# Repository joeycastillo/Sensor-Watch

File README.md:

The Sensor Watch
================

The [Sensor Watch](https://www.sensorwatch.net) is a board replacement for the classic Casio F-91W wristwatch. It is powered by a Microchip SAM L22 microcontroller with built-in segment LCD controller. You can write your own programs for the watch using the provided watch library, program the watch over USB using the built-in UF2 bootloader, and then install the board in your existing watch case to run your own software on your wrist.

Features:
* ARM Cortex M0+ microcontroller
* 32KHz crystal for real-time clock with alarm function
* Ten digit segment LCD, plus five indicator segments
* Three interrupt capable buttons
* Red / green PWM’able LED backlight
* Optional piezo buzzer (requires some light soldering)
* On-board USB Micro B connector
* Reset button with double-tap UF2 bootloader
* Nine-pin flex PCB connector

You may have noticed that there are no sensors on this board. That is by design: rather than pick sensors for you, the goal is to add a tiny flexible PCB with the sensors YOU want, and interface them over the nine-pin connector. The connector provides the following options for power and connectivity:

* 3V power (nominal voltage from a CR2016 coin cell, can drop to ~2.7V)
* An I²C interface with built-in pull-up resistors
* Five general purpose IO pins, which can be configured as:
    * Five analog inputs
    * Five interrupt-capable digital inputs, with internal pull-up or pull-down resistors
    * Five digital outputs
    * SPI controller (with one spare analog / GPIO pin leftover)
    * One UART TX/RX pair (with three GPIO leftover)
    * Up to four PWM pins on two independent TC instances
    * Two external wake inputs that can wake from the ultra-low-power BACKUP mode

| **Pin** | **Digital** | **Interrupt**   | **Analog**    | **I2C**             | **SPI**              | **UART**                 | **PWM**  | **Ext. Wake** |
| :-----: | :---------: | :-------------: | :-----------: | :-----------------: | :------------------: | :----------------------: | :------: | :-----------: |
| **A0**  | PB04        | EIC/EXTINT\[4\] | ADC/AIN\[12\] | —                   | —                    | —                        | —        | —             |
| **SCL** | —           | —               | —             | SCL<br>SERCOM1\[1\] | —                    | —                        | —        | —             |
| **SDA** | —           | —               | —             | SDA<br>SERCOM1\[0\] | —                    | —                        | —        | —             |
| **A1**  | PB01        | EIC/EXTINT\[1\] | ADC/AIN\[9\]  | —                   | SCK<br>SERCOM3\[3\]  | RX<br>SERCOM3\[3\]       | TC3\[1\] | —             |
| **A2**  | PB02        | EIC/EXTINT\[2\] | ADC/AIN\[10\] | —                   | MOSI<br>SERCOM3\[0\] | TX or RX<br>SERCOM3\[0\] | TC2\[0\] | RTC/IN\[1\]   |
| **A3**  | PB03        | EIC/EXTINT\[3\] | ADC/AIN\[11\] | —                   | CS<br>SERCOM3\[1\]   | RX<br>SERCOM3\[1\]       | TC2\[1\] | —             |
| **A4**  | PB00        | EIC/EXTINT\[0\] | ADC/AIN\[8\]  | —                   | MISO<br>SERCOM3\[2\] | TX or RX<br>SERCOM3\[2\] | TC3\[0\] | RTC/IN\[0\]   |

These tiny “sensor boards” have a set outline, and the available area for your electronics is quite small (5.7 × 5.7 × 1 mm). Still, this is plenty of room for an environmental sensor, MEMS accelerometer or magnetometer and a couple of decoupling capacitors. Note that you will likely be limited to QFN and LGA type parts; SOICs are too large, and even SSOP packages are generally too thick. You can find reference designs for several sensor boards in the `PCB/Sensor Boards` directory within this repository.

Getting code on the watch
-------------------------
The watch library in this repository is very work-in-progress, but it should allow you to get started. To create a new project, copy the “starter-project” folder in the apps folder, and write your code in the app.c file.

You will need to install [the GNU Arm Embedded Toolchain](https://developer.arm.com/tools-and-software/open-source-software/developer-tools/gnu-toolchain/gnu-rm/downloads/) to build projects for the watch. The watch library has been tested with the `9-2019-q4-major` version and the `10.3-2021.07` versions. If you're using Debian or Ubuntu, it should be sufficient to `apt install gcc-arm-none-eabi`.

To build your project, open your terminal and navigate to the project's `make` folder, then type `make`.

To install the project onto your Sensor Watch board, plug the watch into your USB port and double tap the tiny Reset button on the back of the board. You should see the LED light up red and begin pulsing. (If it does not, make sure you didn’t plug the board in upside down). Once you see the “WATCHBOOT” drive appear on your desktop, type `make install`. This will convert your compiled program to a UF2 file, and copy it over to the watch.

Using the Movement framework
----------------------------
If you just want to make minor modifications and use existing code, start with the `movement` directory. You can build the default watch firmware with:

```
cd movement/make
make
```

Then copy `movement/make/build/watch.uf2` to your watch. If you'd like to modify which faces are built, see `movement_config.h`.

You may want to test out changes in the emulator first. To do this, you'll need to install [emscripten](https://emscripten.org/), then run:

```
cd movement/make
emmake make
python3 -m http.server -d build-sim
```

Finally, visit [watch.html](http://localhost:8000/watch.html) to see your work.

Hardware Schematics and PCBs
----------------------------

| Name | Color | Schematic | Gerbers |
| ---- | ----- | --------- | ------- |
| Sensorwatch Lite | RED   | [PCB/Main Boards/OSO-SWAT-B1](PCB/Main%20Boards/OSO-SWAT-B1) | [OSO-SWAT-B1-03](PCB/Main%20Boards/OSO-SWAT-B1/OSO-SWAT-B1-03.zip) |
| Sensorwatch      | GREEN | [OSO-SWAT-A1-05](PCB/Main%20Boards/OSO-SWAT-A1/OSO-SWAT-A1-05.sch) (Eagle format) | ? |
| Sensorwatch Pro  | TBD   | TBD  | TBD |

License
-------
Different components of the project are licensed differently, see [LICENSE.md](https://github.com/joeycastillo/Sensor-Watch/blob/main/LICENSE.md).

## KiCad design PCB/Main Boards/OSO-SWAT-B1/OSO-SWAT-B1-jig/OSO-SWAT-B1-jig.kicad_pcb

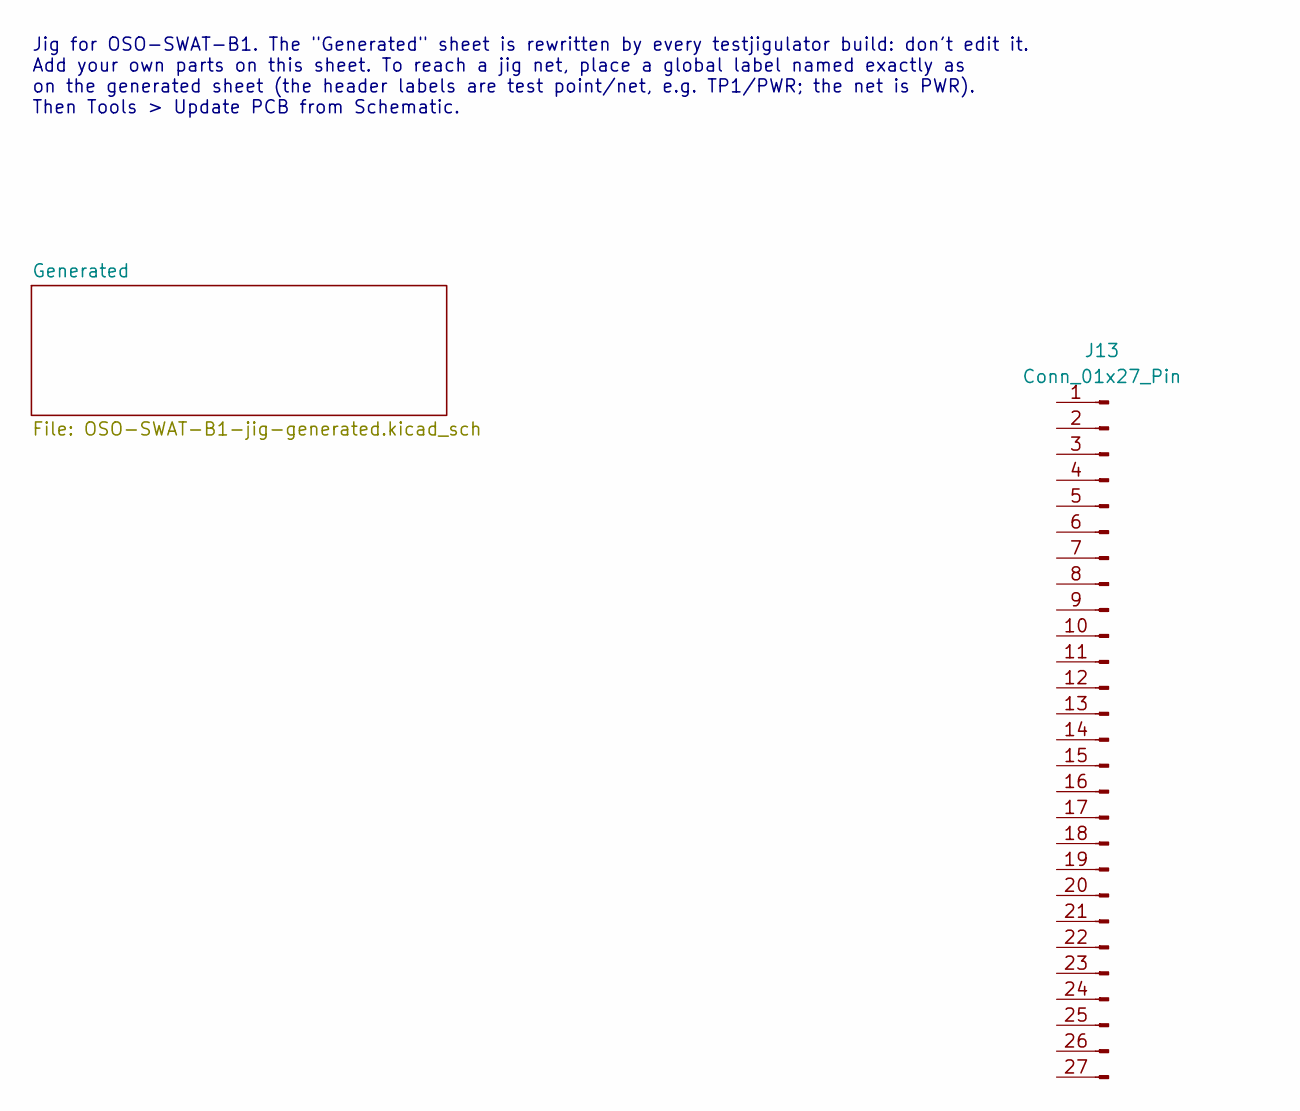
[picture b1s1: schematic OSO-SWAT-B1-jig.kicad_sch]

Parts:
J13: Conn_01x27_Pin; testjig-zebra-footprint

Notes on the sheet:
Jig for OSO-SWAT-B1. The "Generated" sheet is rewritten by every testjigulator build: don't edit it. Add your own parts on this sheet. To reach a jig net, place a global label named exactly as on the generated sheet (the header labels are test point/net, e.g. TP1/PWR; the net is PWR). Then Tools > 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

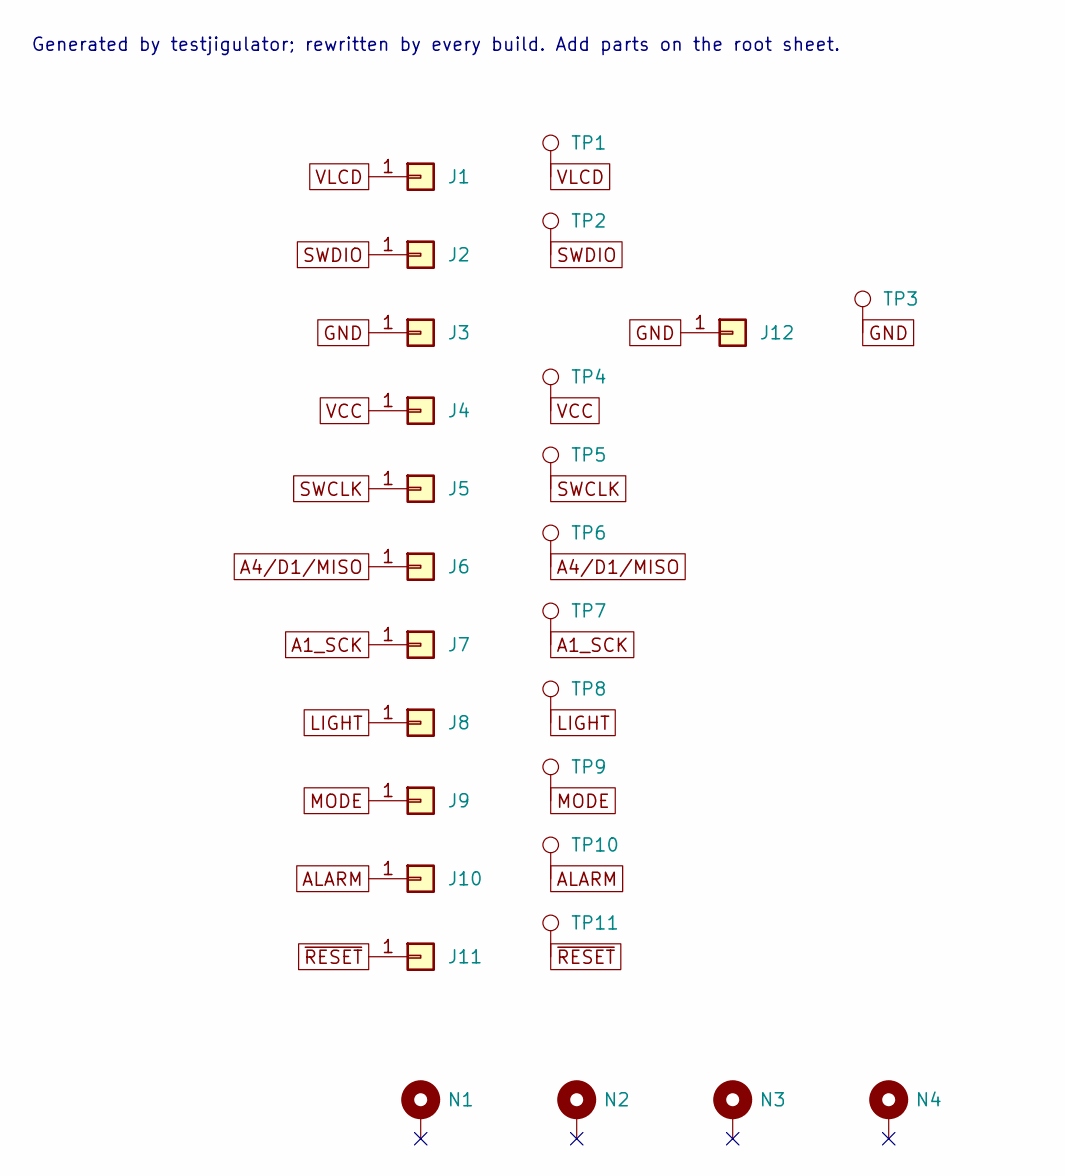
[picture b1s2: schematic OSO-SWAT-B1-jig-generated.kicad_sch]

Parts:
J1: TP1/VLCD; PinHeader_1x01_P2.54mm_Vertical
J2: TP2/SWDIO; PinHeader_1x01_P2.54mm_Vertical
J3: TP3/GND; PinHeader_1x01_P2.54mm_Vertical
J4: TP4/VCC; PinHeader_1x01_P2.54mm_Vertical
J5: TP5/SWCLK; PinHeader_1x01_P2.54mm_Vertical
J6: TP6/A4/D1/MISO; PinHeader_1x01_P2.54mm_Vertical
J7: TP7/A1_SCK; PinHeader_1x01_P2.54mm_Vertical
J8: TP8/LIGHT; PinHeader_1x01_P2.54mm_Vertical
J9: TP9/MODE; PinHeader_1x01_P2.54mm_Vertical
J10: TP10/ALARM; PinHeader_1x01_P2.54mm_Vertical
J11: TP11/~{RESET}; PinHeader_1x01_P2.54mm_Vertical
J12: GND; PinHeader_1x01_P2.54mm_Vertical
N1, N2, N3, N4: SMTSO-M3-1.5ET; LCSC Part C2915632
TP1, TP2, TP3, TP4, TP5, TP6, TP7, TP8, TP9, TP10, TP11: YZ227415084P-01; SMD_BD2.0-D0.6; LCSC Part C5157269

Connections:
A1_SCK: J7.1 (Pin_1_1), TP7.1 (1_1)
A4/D1/MISO: J6.1 (Pin_1_1), TP6.1 (1_1)
ALARM: J10.1 (Pin_1_1), TP10.1 (1_1)
GND: J3.1 (Pin_1_1), J12.1 (Pin_1_1), TP3.1 (1_1)
LIGHT: J8.1 (Pin_1_1), TP8.1 (1_1)
MODE: J9.1 (Pin_1_1), TP9.1 (1_1)
SWCLK: J5.1 (Pin_1_1), TP5.1 (1_1)
SWDIO: J2.1 (Pin_1_1), TP2.1 (1_1)
VCC: J4.1 (Pin_1_1), TP4.1 (1_1)
VLCD: J1.1 (Pin_1_1), TP1.1 (1_1)
~RESET: J11.1 (Pin_1_1), TP11.1 (1_1)

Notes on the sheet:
Generated by testjigulator; rewritten by every build. Add parts on the root sheet.

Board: 2 copper layers, 31 parts (0 on the bottom side), 11 nets, no tracks yet.

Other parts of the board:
HOLDER1: OSO-SWAT-B1-jig-holder; Holder
MH1, MH2: ToolingHole_3mm

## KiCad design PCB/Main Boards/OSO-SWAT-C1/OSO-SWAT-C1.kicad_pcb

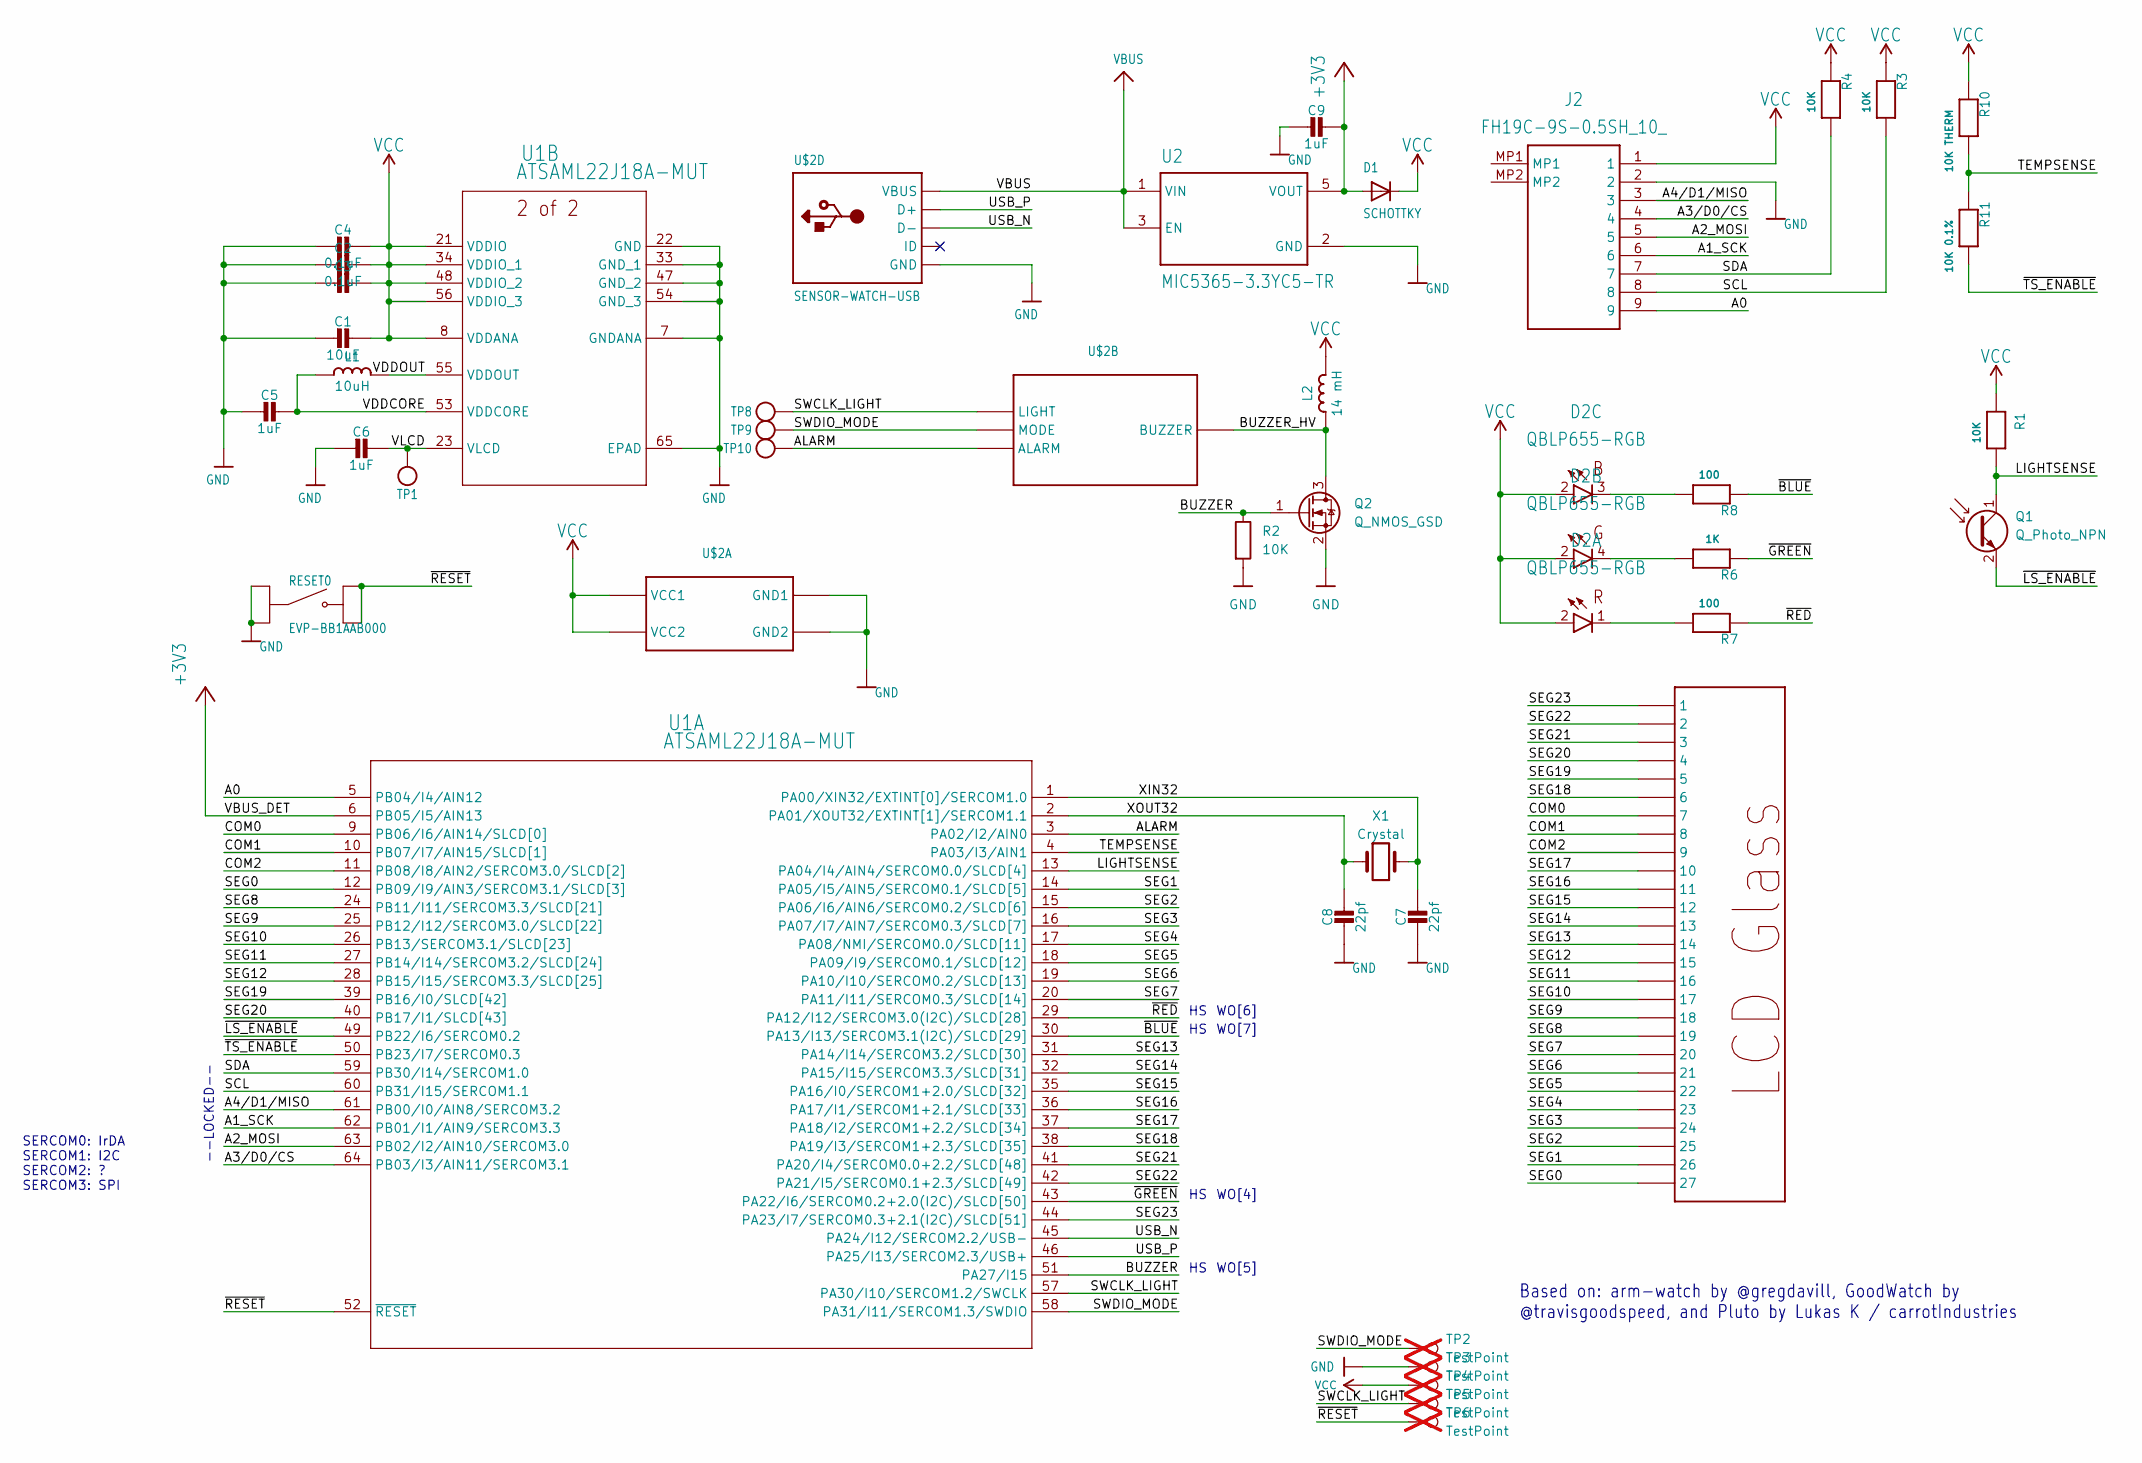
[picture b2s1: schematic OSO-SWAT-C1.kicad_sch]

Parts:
C1: 10uF; C_0603_1608Metric
C2: 0.1uF; C_0201_0603Metric
C3, C4: 0.1uF; C_0603_1608Metric
C5, C6, C9: 1uF; C_0603_1608Metric
C7, C8: 22pf; C_0402_1005Metric
D1: SCHOTTKY; SOD-323F
D2: QBLP655-RGB; LED_QBLP655_RGB
J2: FH19C-9S-0.5SH_10_; FH19C9S05SH10
L1: 10uH; L_0805_2012Metric
L2: 14 mH; ELT3KN
Q1: Q_Photo_NPN; R_0603_1608Metric
Q2: Q_NMOS_GSD; SOT-523
R1, R2, R3, R4: 10K; R_0201_0603Metric
R6: 1K; R_0603_1608Metric
R7, R8: 100; R_0603_1608Metric
R10: 10K THERM; R_0603_1608Metric
R11: 10K 0.1%; R_0603_1608Metric
RESET0: EVP-BB1AAB000; SW_EVP-BB1AAB000
TP1, TP8, TP9, TP10: MICROBUILDER_TESTPOINTROUND1.5MM; MICROBUILDER_TESTPOINT_ROUND_1.5MM
TP2, TP3, TP4, TP5, TP6: TestPoint; TestPoint_Pad_D1.5mm; not fitted
U1: ATSAML22J18A-MUT; QFN64_9X9MC_MCH
U2: MIC5365-3.3YC5-TR; SOT65P210X110-5N
U$2: SENSOR-WATCH-USB; CASIO-F91W-OUTLINE-USB
X1: Crystal; Crystal_SMD_3215-2Pin_3.2x1.5mm

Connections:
+3V3: C9.1, D1.A, U1.6 (PB05/I5/AIN13), U2.5 (VOUT)
/A0: J2.9, U1.5 (PB04/I4/AIN12)
/A1_SCK: J2.6, U1.62 (PB01/I1/AIN9/SERCOM3.3)
/A2_MOSI: J2.5, U1.63 (PB02/I2/AIN10/SERCOM3.0)
/A3/D0/CS: J2.4, U1.64 (PB03/I3/AIN11/SERCOM3.1)
/A4/D1/MISO: J2.3, U1.61 (PB00/I0/AIN8/SERCOM3.2)
/ALARM: TP10.P$1 (P$1_P$1), U1.3 (PA02/I2/AIN0), U$2.ALARM
/BUZZER: Q2.1 (G), R2.1, U1.51 (PA27/I15)
/BUZZER_HV: L2.1, Q2.3 (D), U$2.BUZZER
/COM0: U1.9 (PB06/I6/AIN14/SLCD[0]), U$2.7
/COM1: U1.10 (PB07/I7/AIN15/SLCD[1]), U$2.8
/COM2: U1.11 (PB08/I8/AIN2/SERCOM3.0/SLCD[2]), U$2.9
/LIGHTSENSE: Q1.1 (C), R1.2, U1.13 (PA04/I4/AIN4/SERCOM0.0/SLCD[4])
/SCL: J2.8, R3.2, U1.60 (PB31/I15/SERCOM1.1)
/SDA: J2.7, R4.2, U1.59 (PB30/I14/SERCOM1.0)
/SEG0: U1.12 (PB09/I9/AIN3/SERCOM3.1/SLCD[3]), U$2.27
/SEG1: U1.14 (PA05/I5/AIN5/SERCOM0.1/SLCD[5]), U$2.26
/SEG2: U1.15 (PA06/I6/AIN6/SERCOM0.2/SLCD[6]), U$2.25
/SEG3: U1.16 (PA07/I7/AIN7/SERCOM0.3/SLCD[7]), U$2.24
/SEG4: U1.17 (PA08/NMI/SERCOM0.0/SLCD[11]), U$2.23
/SEG5: U1.18 (PA09/I9/SERCOM0.1/SLCD[12]), U$2.22
/SEG6: U1.19 (PA10/I10/SERCOM0.2/SLCD[13]), U$2.21
/SEG7: U1.20 (PA11/I11/SERCOM0.3/SLCD[14]), U$2.20
/SEG8: U1.24 (PB11/I11/SERCOM3.3/SLCD[21]), U$2.19
/SEG9: U1.25 (PB12/I12/SERCOM3.0/SLCD[22]), U$2.18
/SEG10: U1.26 (PB13/SERCOM3.1/SLCD[23]), U$2.17
/SEG11: U1.27 (PB14/I14/SERCOM3.2/SLCD[24]), U$2.16
/SEG12: U1.28 (PB15/I15/SERCOM3.3/SLCD[25]), U$2.15
/SEG13: U1.31 (PA14/I14/SERCOM3.2/SLCD[30]), U$2.14
/SEG14: U1.32 (PA15/I15/SERCOM3.3/SLCD[31]), U$2.13
/SEG15: U1.35 (PA16/I0/SERCOM1+2.0/SLCD[32]), U$2.12
/SEG16: U1.36 (PA17/I1/SERCOM1+2.1/SLCD[33]), U$2.11
/SEG17: U1.37 (PA18/I2/SERCOM1+2.2/SLCD[34]), U$2.10
/SEG18: U1.38 (PA19/I3/SERCOM1+2.3/SLCD[35]), U$2.6
/SEG19: U1.39 (PB16/I0/SLCD[42]), U$2.5
/SEG20: U1.40 (PB17/I1/SLCD[43]), U$2.4
/SEG21: U1.41 (PA20/I4/SERCOM0.0+2.2/SLCD[48]), U$2.3
/SEG22: U1.42 (PA21/I5/SERCOM0.1+2.3/SLCD[49]), U$2.2
/SEG23: U1.44 (PA23/I7/SERCOM0.3+2.1(I2C)/SLCD[51]), U$2.1
/SWCLK_LIGHT: TP5.1 (1_1), TP8.P$1 (P$1_P$1), U1.57 (PA30/I10/SERCOM1.2/SWCLK), U$2.LIGHT
/SWDIO_MODE: TP2.1 (1_1), TP9.P$1 (P$1_P$1), U1.58 (PA31/I11/SERCOM1.3/SWDIO), U$2.MODE
/TEMPSENSE: R10.2, R11.1, U1.4 (PA03/I3/AIN1)
/USB_N: U1.45 (PA24/I12/SERCOM2.2/USB-), U$2.USB_N (D-)
/USB_P: U1.46 (PA25/I13/SERCOM2.3/USB+), U$2.USB_P (D+)
/VDDCORE: C5.1, L1.1, U1.53 (VDDCORE)
/VDDOUT: L1.2, U1.55 (VDDOUT)
/VLCD: C6.1, TP1.P$1 (P$1_P$1), U1.23 (VLCD)
/XIN32: C7.1, U1.1 (PA00/XIN32/EXTINT[0]/SERCOM1.0), X1.2
/XOUT32: C8.1, U1.2 (PA01/XOUT32/EXTINT[1]/SERCOM1.1), X1.1
/~BLUE: R8.1, U1.30 (PA13/I13/SERCOM3.1(I2C)/SLCD[29])
/~GREEN: R6.1, U1.43 (PA22/I6/SERCOM0.2+2.0(I2C)/SLCD[50])
/~LS_ENABLE: Q1.2 (E), U1.49 (PB22/I6/SERCOM0.2)
/~RED: R7.1, U1.29 (PA12/I12/SERCOM3.0(I2C)/SLCD[28])
/~RESET: RESET0.B1, RESET0.B2, TP6.1 (1_1), U1.52 (~RESET)
/~TS_ENABLE: R11.2, U1.50 (PB23/I7/SERCOM0.3)
GND: C1.2, C2.2, C3.2, C4.2, C5.2, C6.2, C7.2, C8.2, C9.2, J2.2, Q2.2 (S), R2.2, RESET0.A1, RESET0.A2, TP3.1 (1_1), U1.7 (GNDANA), U1.22 (GND), U1.33 (GND_1), U1.47 (GND_2), U1.54 (GND_3), U1.65 (EPAD), U2.2 (GND), U$2.GND, U$2.GND1, U$2.GND2
unnamed: D2.1 (CR), R7.2
unnamed: D2.4 (CG), R6.2
unnamed: D2.3 (CB), R8.2
VBUS: U2.1 (VIN), U2.3 (EN), U$2.VBUS
VCC: C1.1, C2.1, C3.1, C4.1, D1.C, D2.2 (A), J2.1, L2.2, R1.1, R3.1, R4.1, R10.1, TP4.1 (1_1), U1.8 (VDDANA), U1.21 (VDDIO), U1.34 (VDDIO_1), U1.48 (VDDIO_2), U1.56 (VDDIO_3), U$2.VCC1, U$2.VCC2

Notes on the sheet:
Based on: arm-watch by @gregdavill, GoodWatch by @travisgoodspeed, and Pluto by Lukas K / carrotIndustries
WO[7]
SERCOM0: IrDA SERCOM1: I2C SERCOM2: ? SERCOM3: SPI
--LOCKED--
WO[6]
WO[4]
WO[5]

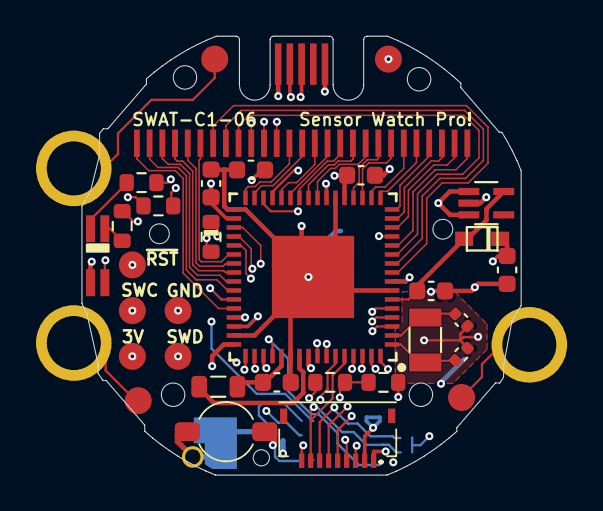
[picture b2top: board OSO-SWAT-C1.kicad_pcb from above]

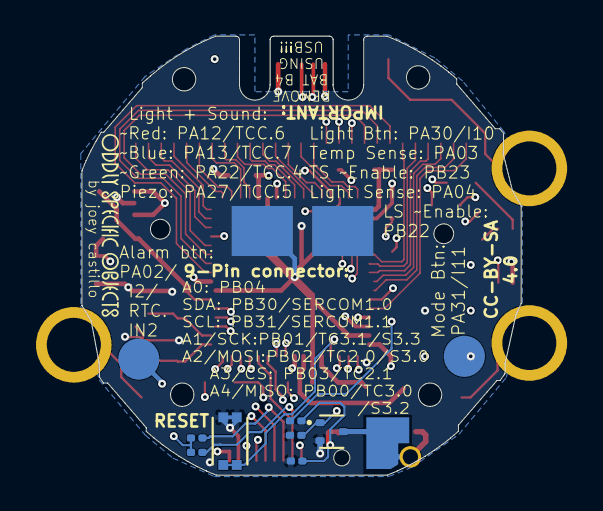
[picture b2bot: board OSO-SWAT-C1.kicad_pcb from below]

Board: 4 copper layers, 24.4 x 24.4 mm, 39 parts (7 on the bottom side), 61 nets.

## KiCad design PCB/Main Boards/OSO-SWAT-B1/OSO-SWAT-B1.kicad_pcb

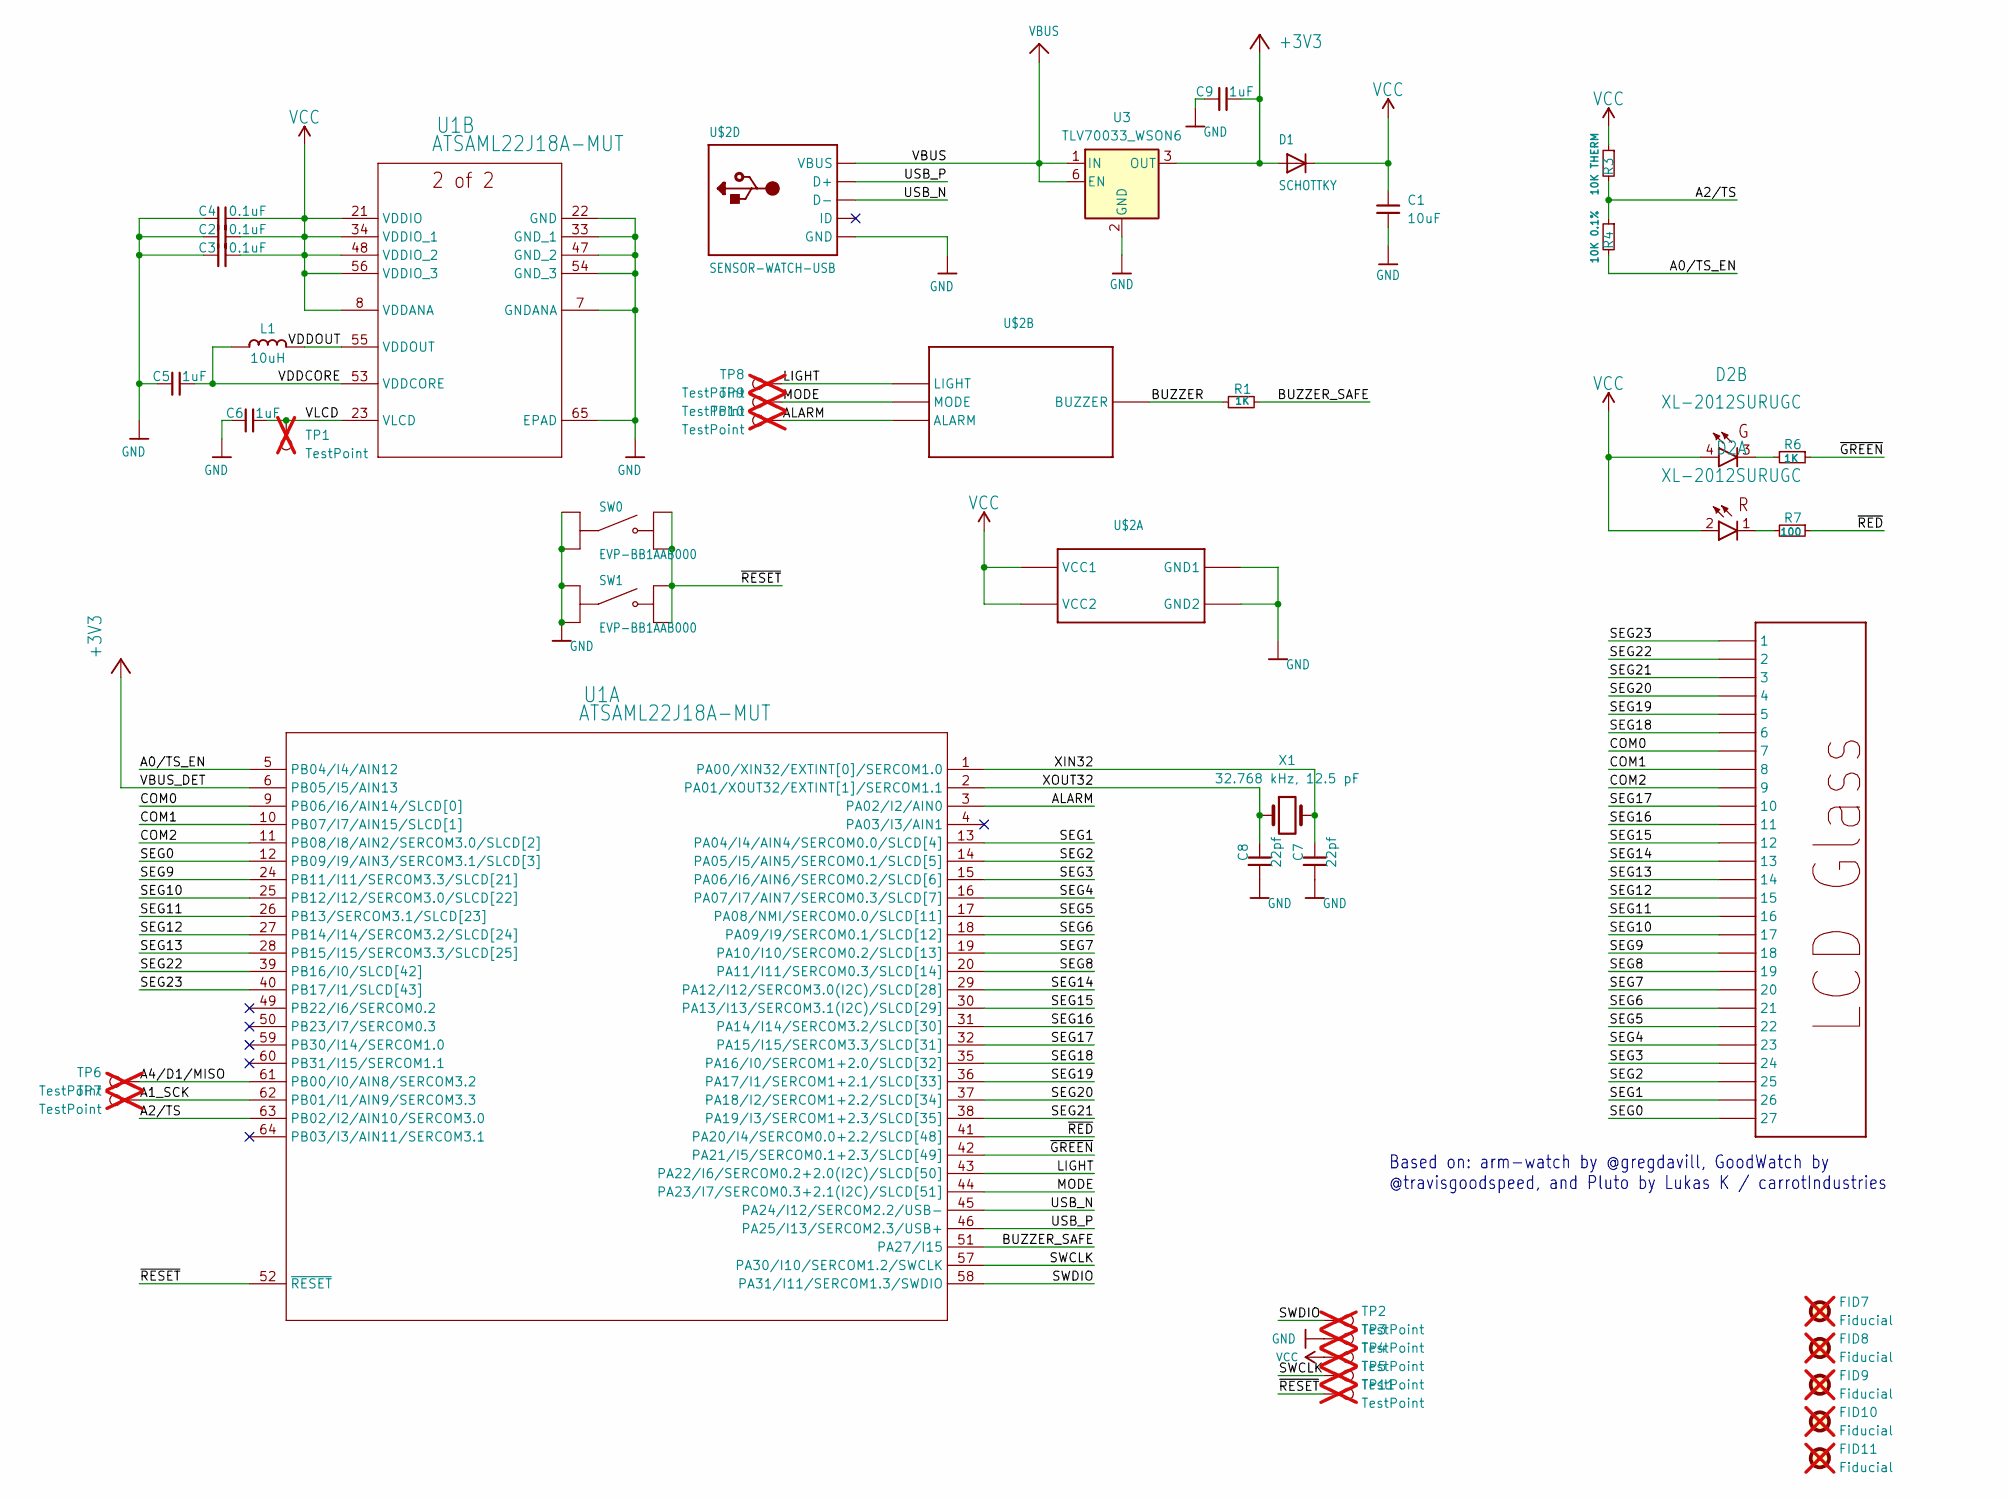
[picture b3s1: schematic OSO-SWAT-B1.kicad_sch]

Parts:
C1: 10uF; _0603MP; LCSC Part C19702
C2, C3, C4: 0.1uF; _0402MP; LCSC Part C1525
C5, C6, C9: 1uF; _0402MP; LCSC Part C52923
C7, C8: 22pf; _0402MP; LCSC Part C1555
D1: SCHOTTKY; SOD-323F; LCSC Part C2972951
D2: XL-2012SURUGC; LED-SMD_4P-L2.0-W1.3-RD-TL; LCSC Part C965845
FID7, FID8, FID9, FID10, FID11: Fiducial; Fiducial_0.75mm_Mask1.5mm; not fitted
L1: 10uH; MICROBUILDER__0805MP; LCSC Part C139245
R1: 1K; _0603MP; LCSC Part C21190
R3: 10K THERM; _0603MP; LCSC Part C440252
R4: 10K 0.1%; _0603MP; LCSC Part C95204
R6: 1K; _0402MP; LCSC Part C11702
R7: 100; _0402MP; LCSC Part C25076
SW0, SW1: EVP-BB1AAB000; SW_EVP-BB1AAB000; LCSC Part C5185477
TP1, TP2, TP3, TP4, TP5, TP6, TP7, TP8, TP9, TP10, TP11: TestPoint; TestPoint_Pad_D1.5mm; not fitted
U1: ATSAML22J18A-MUT; QFN64_9X9MC_MCH; LCSC Part C618315
U3: TLV70033_WSON6; WSON-6_1.5x1.5mm_P0.5mm; LCSC Part C97256
U$2: SENSOR-WATCH-USB; CASIO-F91W-OUTLINE-USB
X1: 32.768 kHz, 12.5 pF; Crystal_SMD_3215-2Pin_3.2x1.5mm; LCSC Part C2613043

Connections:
+3V3: C9.1, D1.A, U1.6 (PB05/I5/AIN13), U3.3 (OUT)
/A0/TS_EN: R4.2, U1.5 (PB04/I4/AIN12)
/A1_SCK: TP7.1 (1_1), U1.62 (PB01/I1/AIN9/SERCOM3.3)
/A2/TS: R3.2, R4.1, U1.63 (PB02/I2/AIN10/SERCOM3.0)
/A4/D1/MISO: TP6.1 (1_1), U1.61 (PB00/I0/AIN8/SERCOM3.2)
/ALARM: TP10.1 (1_1), U1.3 (PA02/I2/AIN0), U$2.ALARM
/BUZZER: R1.1, U$2.BUZZER
/BUZZER_SAFE: R1.2, U1.51 (PA27/I15)
/COM0: U1.9 (PB06/I6/AIN14/SLCD[0]), U$2.7
/COM1: U1.10 (PB07/I7/AIN15/SLCD[1]), U$2.8
/COM2: U1.11 (PB08/I8/AIN2/SERCOM3.0/SLCD[2]), U$2.9
/LIGHT: TP8.1 (1_1), U1.43 (PA22/I6/SERCOM0.2+2.0(I2C)/SLCD[50]), U$2.LIGHT
/MODE: TP9.1 (1_1), U1.44 (PA23/I7/SERCOM0.3+2.1(I2C)/SLCD[51]), U$2.MODE
/SEG0: U1.12 (PB09/I9/AIN3/SERCOM3.1/SLCD[3]), U$2.27
/SEG1: U1.13 (PA04/I4/AIN4/SERCOM0.0/SLCD[4]), U$2.26
/SEG2: U1.14 (PA05/I5/AIN5/SERCOM0.1/SLCD[5]), U$2.25
/SEG3: U1.15 (PA06/I6/AIN6/SERCOM0.2/SLCD[6]), U$2.24
/SEG4: U1.16 (PA07/I7/AIN7/SERCOM0.3/SLCD[7]), U$2.23
/SEG5: U1.17 (PA08/NMI/SERCOM0.0/SLCD[11]), U$2.22
/SEG6: U1.18 (PA09/I9/SERCOM0.1/SLCD[12]), U$2.21
/SEG7: U1.19 (PA10/I10/SERCOM0.2/SLCD[13]), U$2.20
/SEG8: U1.20 (PA11/I11/SERCOM0.3/SLCD[14]), U$2.19
/SEG9: U1.24 (PB11/I11/SERCOM3.3/SLCD[21]), U$2.18
/SEG10: U1.25 (PB12/I12/SERCOM3.0/SLCD[22]), U$2.17
/SEG11: U1.26 (PB13/SERCOM3.1/SLCD[23]), U$2.16
/SEG12: U1.27 (PB14/I14/SERCOM3.2/SLCD[24]), U$2.15
/SEG13: U1.28 (PB15/I15/SERCOM3.3/SLCD[25]), U$2.14
/SEG14: U1.29 (PA12/I12/SERCOM3.0(I2C)/SLCD[28]), U$2.13
/SEG15: U1.30 (PA13/I13/SERCOM3.1(I2C)/SLCD[29]), U$2.12
/SEG16: U1.31 (PA14/I14/SERCOM3.2/SLCD[30]), U$2.11
/SEG17: U1.32 (PA15/I15/SERCOM3.3/SLCD[31]), U$2.10
/SEG18: U1.35 (PA16/I0/SERCOM1+2.0/SLCD[32]), U$2.6
/SEG19: U1.36 (PA17/I1/SERCOM1+2.1/SLCD[33]), U$2.5
/SEG20: U1.37 (PA18/I2/SERCOM1+2.2/SLCD[34]), U$2.4
/SEG21: U1.38 (PA19/I3/SERCOM1+2.3/SLCD[35]), U$2.3
/SEG22: U1.39 (PB16/I0/SLCD[42]), U$2.2
/SEG23: U1.40 (PB17/I1/SLCD[43]), U$2.1
/SWCLK: TP5.1 (1_1), U1.57 (PA30/I10/SERCOM1.2/SWCLK)
/SWDIO: TP2.1 (1_1), U1.58 (PA31/I11/SERCOM1.3/SWDIO)
/USB_N: U1.45 (PA24/I12/SERCOM2.2/USB-), U$2.USB_N (D-)
/USB_P: U1.46 (PA25/I13/SERCOM2.3/USB+), U$2.USB_P (D+)
/VDDCORE: C5.1, L1.1, U1.53 (VDDCORE)
/VDDOUT: L1.2, U1.55 (VDDOUT)
/VLCD: C6.1, TP1.1 (1_1), U1.23 (VLCD)
/XIN32: C7.1, U1.1 (PA00/XIN32/EXTINT[0]/SERCOM1.0), X1.2
/XOUT32: C8.1, U1.2 (PA01/XOUT32/EXTINT[1]/SERCOM1.1), X1.1
/~GREEN: R6.1, U1.42 (PA21/I5/SERCOM0.1+2.3/SLCD[49])
/~RED: R7.1, U1.41 (PA20/I4/SERCOM0.0+2.2/SLCD[48])
/~RESET: SW0.B1, SW0.B2, SW1.B1, SW1.B2, TP11.1 (1_1), U1.52 (~RESET)
GND: C1.2, C2.2, C3.2, C4.2, C5.2, C6.2, C7.2, C8.2, C9.2, SW0.A1, SW0.A2, SW1.A1, SW1.A2, TP3.1 (1_1), U1.7 (GNDANA), U1.22 (GND), U1.33 (GND_1), U1.47 (GND_2), U1.54 (GND_3), U1.65 (EPAD), U3.2 (GND), U$2.GND, U$2.GND1, U$2.GND2
unnamed: D2.1 (C), R7.2
unnamed: D2.3 (C), R6.2
VBUS: U3.1 (IN), U3.6 (EN), U$2.VBUS
VCC: C1.1, C2.1, C3.1, C4.1, D1.C, D2.2 (A), D2.4 (A), R3.1, TP4.1 (1_1), U1.8 (VDDANA), U1.21 (VDDIO), U1.34 (VDDIO_1), U1.48 (VDDIO_2), U1.56 (VDDIO_3), U$2.VCC1, U$2.VCC2

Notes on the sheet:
Based on: arm-watch by @gregdavill, GoodWatch by @travisgoodspeed, and Pluto by Lukas K / carrotIndustries

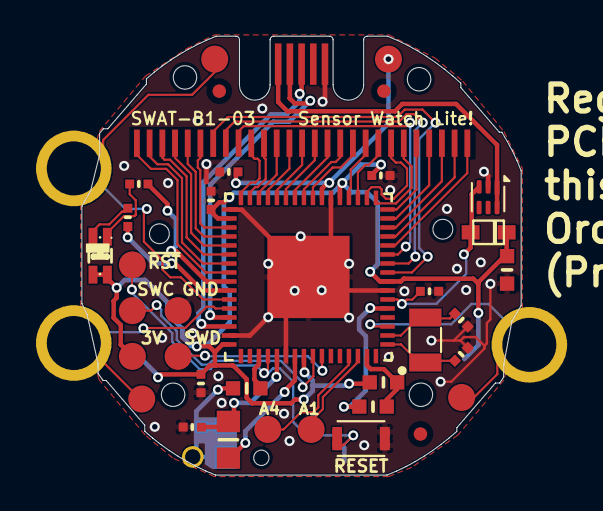
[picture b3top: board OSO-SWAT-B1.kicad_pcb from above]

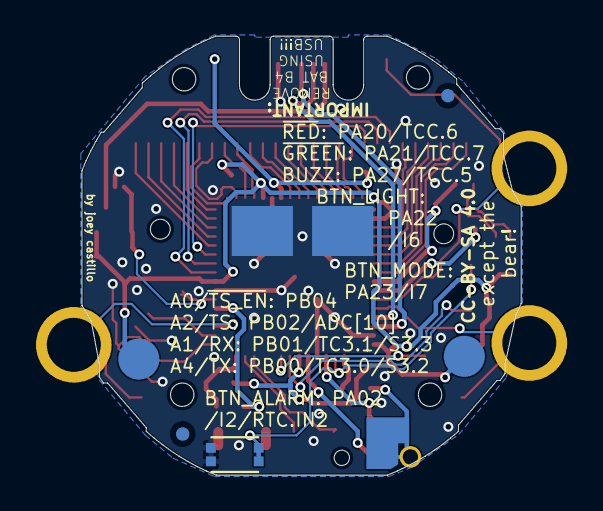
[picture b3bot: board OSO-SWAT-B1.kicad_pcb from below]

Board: 2 copper layers, 24.4 x 24.4 mm, 39 parts (3 on the bottom side), 54 nets.

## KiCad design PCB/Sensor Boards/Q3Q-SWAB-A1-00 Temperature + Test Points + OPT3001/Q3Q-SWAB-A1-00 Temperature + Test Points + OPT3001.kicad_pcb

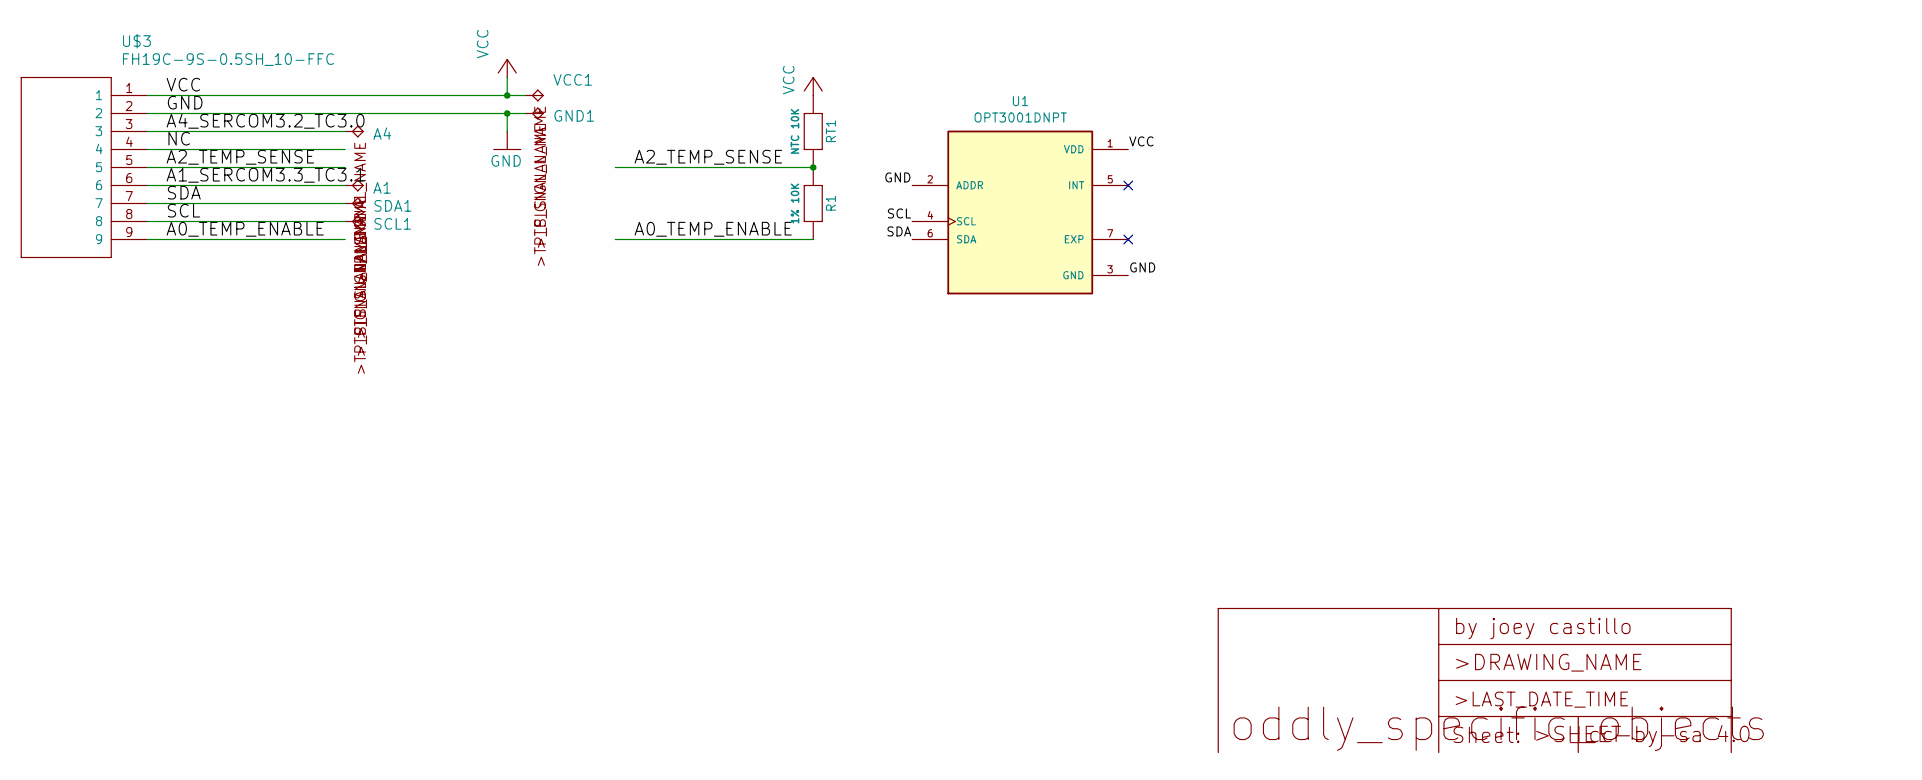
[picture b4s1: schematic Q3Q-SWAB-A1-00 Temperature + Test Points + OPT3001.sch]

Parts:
A1, A4: TPB1,27; B1,27
GND1: TPB1,27; B1,27
R1: 1% 10K; _0603MP
RT1: NTC 10K; _0603MP
SCL1: TPB1,27; B1,27
SDA1: TPB1,27; B1,27
U1: OPT3001DNPT; SON65P200X200X65-7N; PARTREV 01/2018
U$3: FH19C-9S-0.5SH_10-FFC; FH19C9S05SH10-FFC
VCC1: TPB1,27; B1,27

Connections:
/A0_TEMP_ENABLE: R1.2, U$3.9
/A1_SERCOM3.3_TC3.1: A1.TP, U$3.6
/A2_TEMP_SENSE: R1.1, RT1.2, U$3.5
/A4_SERCOM3.2_TC3.0: A4.TP, U$3.3
/NC: U$3.4
/SCL: SCL1.TP, U1.4 (SCL), U$3.8
/SDA: SDA1.TP, U1.6 (SDA), U$3.7
GND: GND1.TP, U1.2 (ADDR), U1.3 (GND), U$3.2
VCC: RT1.1, U1.1 (VDD), U$3.1, VCC1.TP

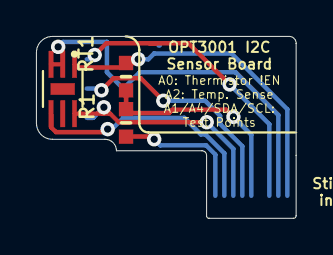
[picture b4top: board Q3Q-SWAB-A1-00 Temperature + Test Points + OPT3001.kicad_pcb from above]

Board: 2 copper layers, 14.4 x 10.1 mm, 10 parts (0 on the bottom side), 8 nets.

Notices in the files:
PCB/Main Boards/OSO-SWAT-B1/OSO-SWAT-B1.kicad_pcb:
CC-BY-SA 4.0
PCB/Main Boards/OSO-SWAT-C1/OSO-SWAT-C1.kicad_pcb:
CC-BY-SA
parts and their libraries:
Copyright 2021 Accelerated Designs. All rights reserved.
